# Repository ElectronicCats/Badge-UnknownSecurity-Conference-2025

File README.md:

# Unknown Security Conference Badge

## Technology

- CH32V003
- LEDs
- Display OLED
- 2x AAA Battery Holder
- Shitty Addon Connector

## Getting Started

Your badge comes with a pre-installed firmware, but in case you need to reprogram it, you can use the firmware.hex from the release section.

If you want to build your own firmware, you can use [MounRiver Studio](http://mounriver.com/).

## Gratitude
Do you want to say thank you? Tag these companies on social networks and show them your badge, thanks to them it is possible

- [Electronic Cats](https://electroniccats.com/)
- [Unknown Security Conference](https://unknowncon.pe/)

## License

Electronic Cats invests time and resources providing this open source design, please support Electronic Cats and open-source hardware by purchasing products from Electronic Cats!

Designed by Electronic Cats.

Hardware released under an CERN Open Hardware Licence v1.2. See the LICENSE_HARDWARE file for more information.

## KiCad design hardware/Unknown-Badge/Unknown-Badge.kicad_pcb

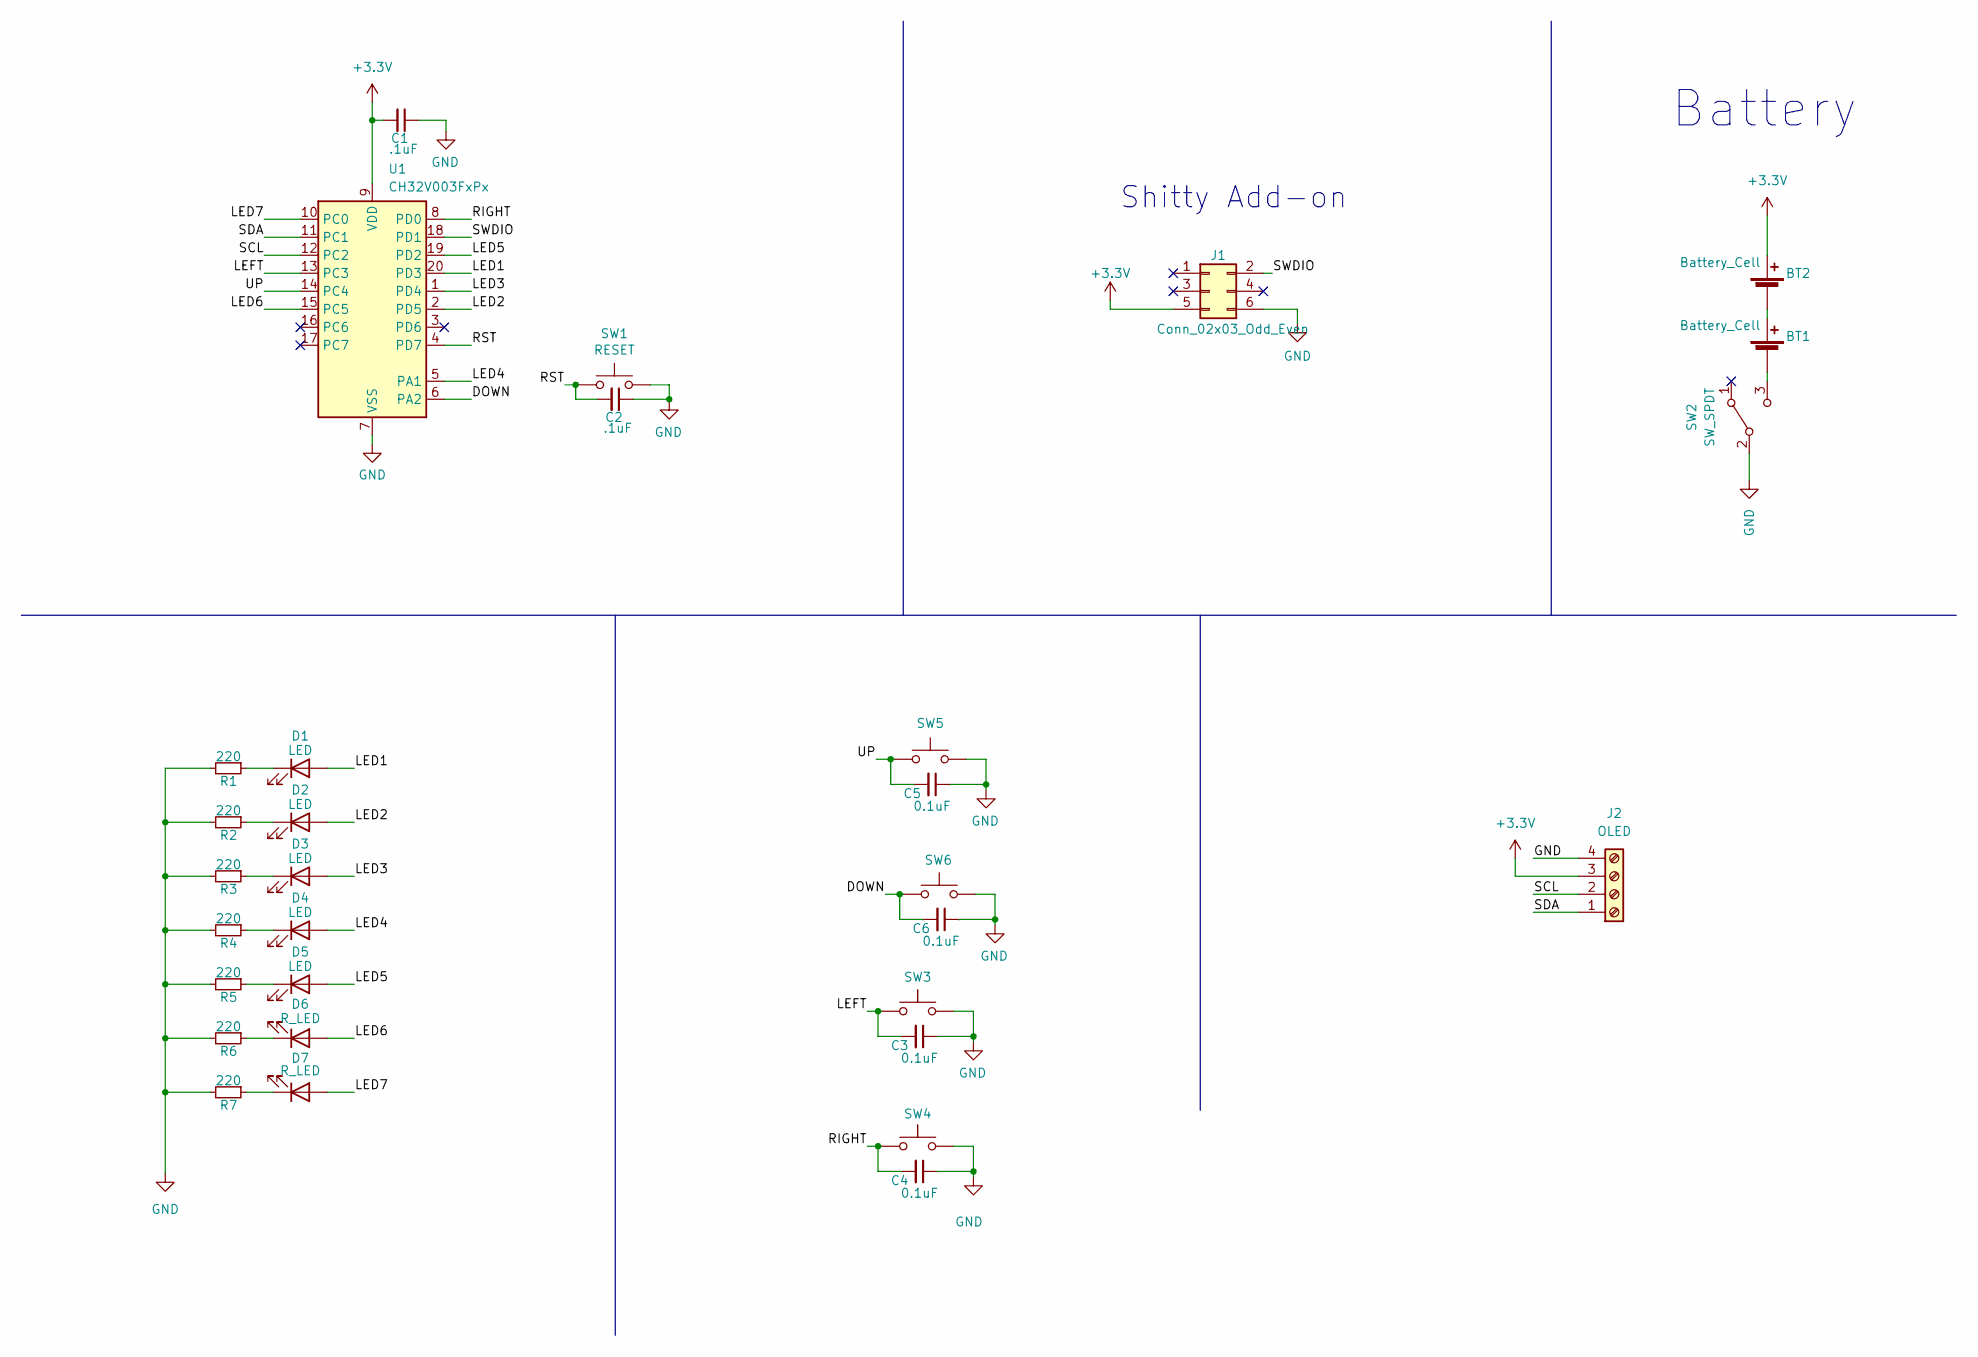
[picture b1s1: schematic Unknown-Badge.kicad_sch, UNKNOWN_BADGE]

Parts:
BT1, BT2: Battery_Cell; BatteryHolder_Keystone_2466_1xAAA; LCSC# C5290189
C1, C2: .1uF; C_0603_1608Metric; LCSC# C478888
C3, C4, C5, C6: 0.1uF; C_0603_1608Metric; LCSC# C478888
D1, D2, D3, D4, D5: LED; LED_0603_1608Metric; LCSC# C434424
D6, D7: R_LED; LYT77K-K2M1
J1: Conn_02x03_Odd_Even; PinHeader_2x03_P2.54mm_Vertical_SMD; LCSC# C3975148
J2: OLED; Display OLED 128 x32
R1, R2, R3, R4, R5, R6, R7: 220; R_0603_1608Metric; LCSC# C22962
SW1: RESET; SW_SPST_TL3342; LCSC# C318889
SW2: SW_SPDT; MSK12C02; LCSC# C431540
SW3, SW4, SW5, SW6: SW_SPST_TL3342; LCSC# C318889
U1: CH32V003FxPx; TSSOP-20_4.4x6.5mm_P0.65mm; LCSC# C5187096

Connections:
+3.3V: BT2.1 (+), C1.2, J1.5, J2.3, U1.9 (VDD)
/DOWN: C6.2, SW6.2, U1.6 (PA2)
/LED1: D1.2 (A), U1.20 (PD3)
/LED2: D2.2 (A), U1.2 (PD5)
/LED3: D3.2 (A), U1.1 (PD4)
/LED4: D4.2 (A), U1.5 (PA1)
/LED5: D5.2 (A), U1.19 (PD2)
/LED6: D6.2 (A), U1.15 (PC5)
/LED7: D7.2 (A), U1.10 (PC0)
/LEFT: C3.2, SW3.2, U1.13 (PC3)
/RIGHT: C4.2, SW4.2, U1.8 (PD0)
/RST: C2.2, SW1.2, U1.4 (PD7)
/SCL: J2.2, U1.12 (PC2)
/SDA: J2.1, U1.11 (PC1)
/SWDIO: J1.2, U1.18 (PD1)
/UP: C5.2, SW5.2, U1.14 (PC4)
GND: C1.1, C2.1, C3.1, C4.1, C5.1, C6.1, J1.6, J2.4, R1.2, R2.2, R3.2, R4.2, R5.2, R6.2, R7.2, SW1.1, SW2.2 (B), SW3.1, SW4.1, SW5.1, SW6.1, U1.7 (VSS)
unnamed: BT1.1 (+), BT2.2 (-)
unnamed: BT1.2 (-), SW2.3 (C)
unnamed: D1.1 (K), R1.1
unnamed: D2.1 (K), R2.1
unnamed: D3.1 (K), R3.1
unnamed: D4.1 (K), R4.1
unnamed: D5.1 (K), R5.1
unnamed: D6.1 (K), R6.1
unnamed: D7.1 (K), R7.1

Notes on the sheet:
Shitty Add-on
Battery

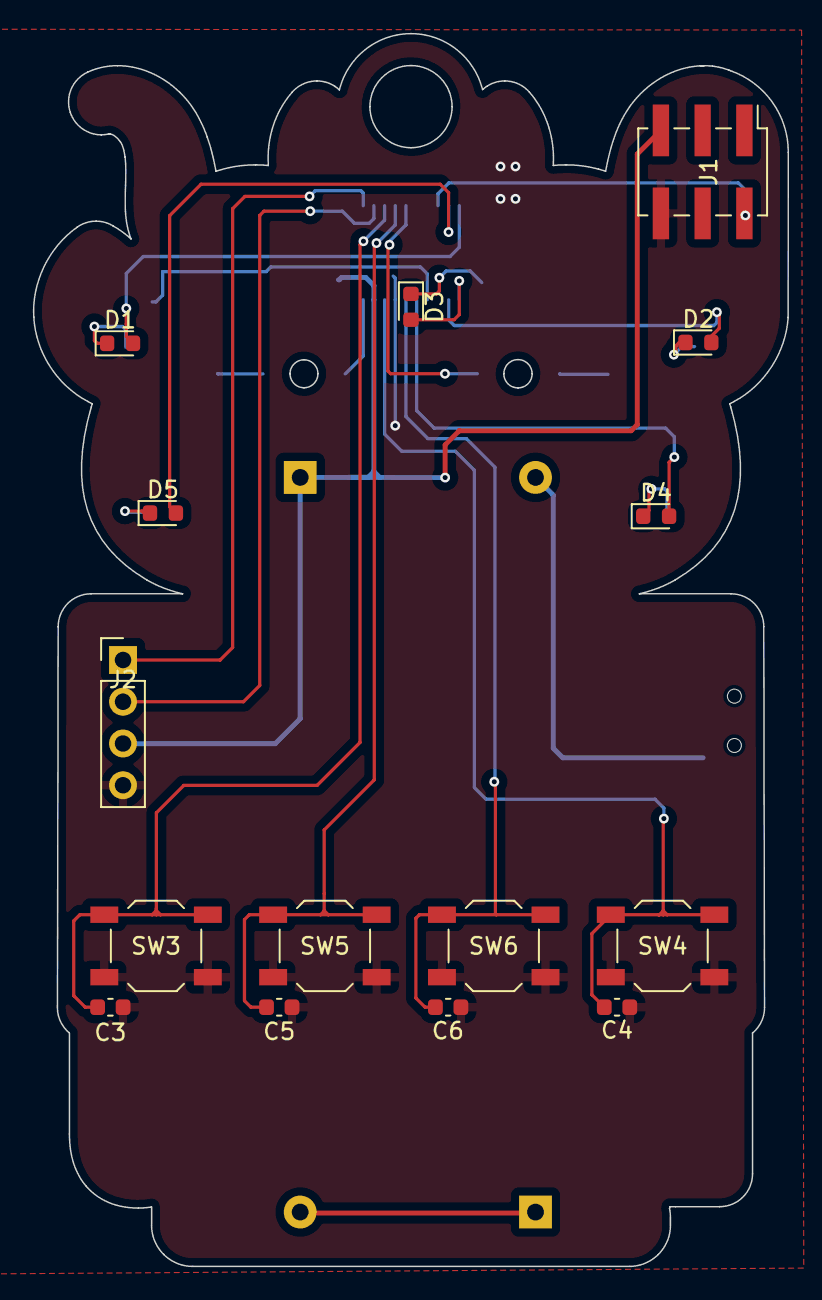
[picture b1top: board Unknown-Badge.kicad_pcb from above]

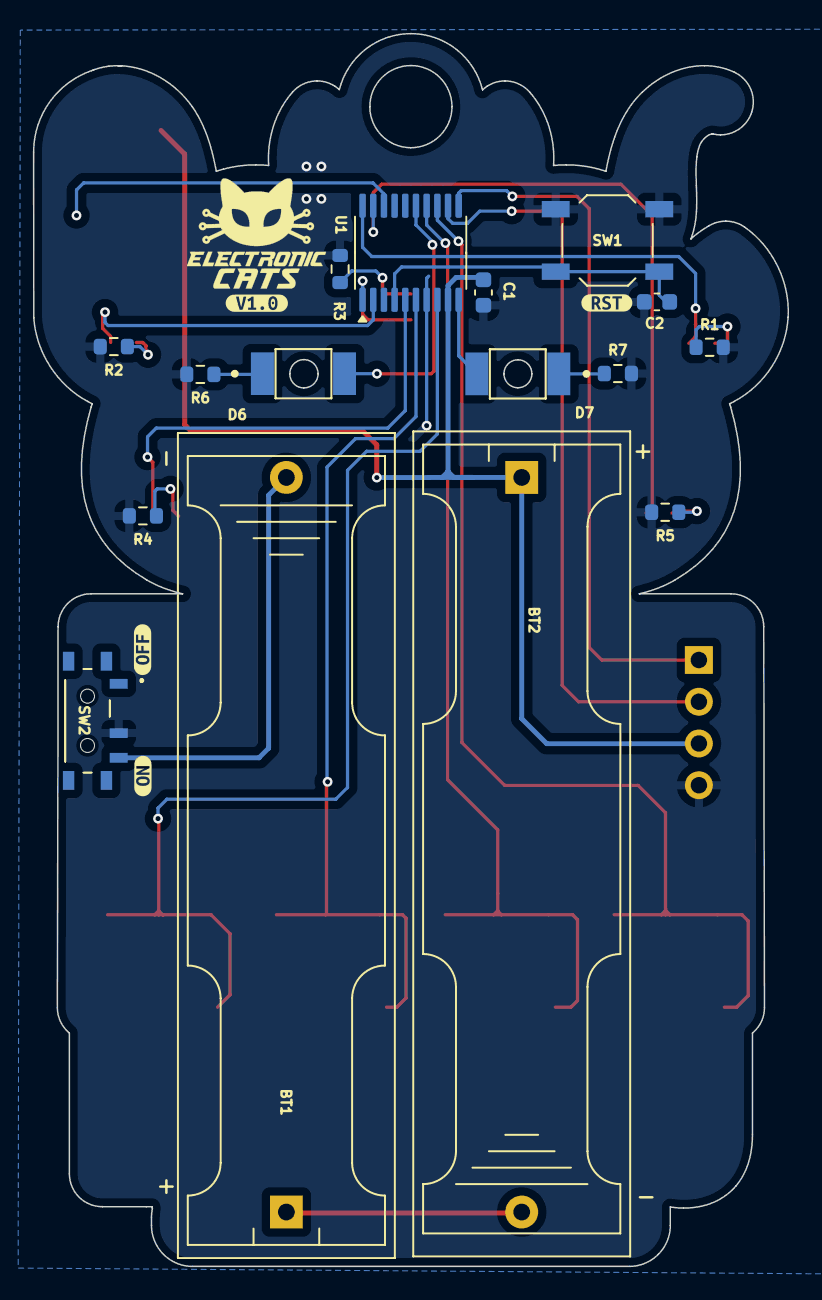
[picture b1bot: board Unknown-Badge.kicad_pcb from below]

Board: 2 copper layers, 45.9 x 75.0 mm, 35 parts (20 on the bottom side), 26 nets.

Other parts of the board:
kibuzzard-6839DD39: G***; kibuzzard-6839DD39
kibuzzard-6839DD63: G***; kibuzzard-6839DD63
kibuzzard-6839DD94: G***; kibuzzard-6839DD94
kibuzzard-6839DDBA: G***; kibuzzard-6839DDBA

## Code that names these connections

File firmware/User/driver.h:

// ===================================================================================
// Tiny Joypad Drivers for CH32V003                                           *
// v1.0 *
// ===================================================================================
//
// MCU abstraction layer.
// 2023 by Stefan Wagner:   https://github.com/wagiminator

#pragma once

#ifdef __cplusplus
extern "C" {
#endif

#include <stdbool.h>
#include "ch32v00x.h"
#include "gpio.h"
#include "oled_min.h"

// #define DEBUG_ENABLE 1
// #define DEV_VERSION 1

#define APP_DBG(X...)             \
  if (1) {                        \
    PRINT("[%s] ", __FUNCTION__); \
    PRINT(X);                     \
    PRINT("\r\n");                \
  }

// Pin assignments
#define BUTTON_RIGHT_PIN PD0
#define BUTTON_LEFT_PIN  PC3
#define BUTTON_UP_PIN    PC4
#ifdef DEV_VERSION
  #define BUTTON_DOWN_PIN PC6
#else
  #define BUTTON_DOWN_PIN PA2
#endif

#define LED1_PIN PD3
#define LED2_PIN PD5
#define LED3_PIN PD4
#define LED4_PIN PA1
#define LED5_PIN PD2
#define LED6_PIN PC5
#define LED7_PIN PC0

#define PIN_SCL PC2  // pin connected to OLED (I2C SCL)
#define PIN_SDA PC1  // pin connected to OLED (I2C SDA)

// Delays
#define JOY_DLY_ms Delay_Ms
#define JOY_DLY_us Delay_Us

// Additional Defines
#define abs(n) ((n >= 0) ? (n) : (-(n)))

// Game slow-down delay
#define JOY_SLOWDOWN()  // DLY_ms(10)

extern uint8_t leds[];
extern uint8_t leds_count;

#define JOY_pad_pressed()  (ADC_read() > 10)
#define JOY_pad_released() (ADC_read() <= 10)

// static inline void JOY_init(void);
void JOY_init(void);

// OLED commands
#define JOY_OLED_init            OLED_init
#define JOY_OLED_end             I2C_stop
#define JOY_OLED_send(b)         I2C_write(b)
#define JOY_OLED_send_command(c) OLED_send_command(c)
#define JOY_OLED_data_start(y) \
  {                            \
    OLED_setpos(0, y);         \
    OLED_data_start();         \
  }

// Buttons
#define JOY_pad_pressed()  (ADC_read() > 10)
#define JOY_pad_released() (ADC_read() <= 10)

uint8_t joy_up_pressed(void);
uint8_t joy_down_pressed(void);
uint8_t joy_left_pressed(void);
uint8_t joy_right_pressed(void);
uint16_t JOY_random(void);
long map(long x, long in_min, long in_max, long out_min, long out_max);

#ifdef __cplusplus
};
#endif

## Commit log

2025-05-21 feat(Hw):Preject_Added
2025-05-22 fest(Hw):PCB_Sch_Update
2025-05-22 feat(Hw):3D_Models_Added
2025-05-30 feat(Hw):Labels_updated
2025-06-10 chore: add firmware project
2025-06-10 chore: rename project
2025-06-10 fix: remove led 8
2025-06-11 chore: add firmware build files
2025-06-11 chore: add licenses
2025-06-11 docs: add readme doc
